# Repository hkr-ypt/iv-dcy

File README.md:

# IV-DCY USB reference board

IV-DCY is a small open-source USB device: a two-layer STM32F042 board and its
firmware. The board enumerates as a USB CDC-ACM serial port and answers a few
text commands (`PING`, `VERSION`, `INFO`, ...).

This project is the public reference implementation of the IV-DCY USB
identity: the vendor/product ID, the descriptors and the CDC-ACM command
interface. **It is not a measurement instrument.** The board has no
current–voltage (I–V) or other measurement hardware, and the firmware has no
measurement, calibration or instrument-control code. Everything here is a
complete, minimal USB device in its own right.

| | |
|---|---|
| USB ID | VID `0x1209` (pid.codes), PID `0x6767`: the PID this project will request from pid.codes. **Not yet assigned.** |
| USB function | USB 2.0 full speed, one CDC-ACM interface (virtual serial port), bus powered |
| MCU | STMicroelectronics STM32F042K6T6 (Cortex-M0, 48 MHz, 32 KiB flash, 6 KiB RAM, crystal-less USB) |
| Board | 28 × 36 mm, 2 layers, 18 components, USB-C |
| Licences | hardware CERN-OHL-S-2.0, firmware/software MIT (see [Licensing](#licensing)) |
| Status | Designed and checked in software only. **Not yet fabricated or tested on hardware**; see [docs/verification.md](docs/verification.md). |

## What the hardware does

The board is a bus-powered USB device with nothing on it but what a USB
device needs:

| Ref | Part | Purpose |
|---|---|---|
| J1 | GCT USB4105-GF-A USB-C receptacle (USB 2.0) | USB connection. The 5.1 kΩ R1/R2 on CC1/CC2 identify the board as a USB-C sink, so hosts supply 5 V. |
| U3 | ST USBLC6-2SC6 | ESD protection on D+/D− (flow-through layout), referenced to VBUS |
| U2, C1, C2 | Microchip MCP1700-3.3 LDO, 1 µF / 4.7 µF | 3.3 V from VBUS |
| U1, C3–C7 | ST STM32F042K6T6 + decoupling and NRST capacitor | USB full-speed device with on-chip D+ pull-up. Its 48 MHz RC oscillator is trimmed to the USB frame clock, so no crystal is needed. |
| SW1, R3 | BOOT push-button, 10 kΩ pull-down on PB8/BOOT0 | Held while plugging in: starts ST's USB DFU bootloader in ROM. Afterwards it is readable as a button. |
| D1, R4 | green LED on PA4 | status |
| J2 | ARM Cortex 10-pin 1.27 mm header | SWD programming/debugging |

Schematic: [hardware/docs/iv_dcy-schematic.pdf](hardware/docs/iv_dcy-schematic.pdf).
BOM: [hardware/bom/iv_dcy-bom.csv](hardware/bom/iv_dcy-bom.csv).
Design notes: [hardware/README.md](hardware/README.md).

## What the firmware does

The firmware sets up the 48 MHz clock and USB, then runs the TinyUSB device
stack. It enumerates as a CDC-ACM serial port and replies to line-based
commands:

| Command | Reply |
|---|---|
| `PING` | `PONG` |
| `VERSION` | firmware version, e.g. `0.1.0` |
| `INFO` | `IV-DCY USB reference fw=0.1.0 vid=0x1209 pid=0x6767 serial=<24 hex digits>` |
| `LED ON` / `LED OFF` / `LED AUTO` | `OK` (AUTO: LED shows the USB state) |
| `BUTTON` | `PRESSED` or `RELEASED` |
| `HELP` | list of commands |

The full descriptor and protocol description is in
[docs/usb-interface.md](docs/usb-interface.md). The firmware is about 11 KiB.
Build, test and flashing details are in [firmware/README.md](firmware/README.md).

## Repository layout

```
hardware/            board design (CERN-OHL-S-2.0)
  skidl/             circuit source (SKiDL) + schematic writer
  layout/            PCB placement and routing source (KiCad pcbnew script)
  kicad/             generated, editable KiCad 9 project: .kicad_sch, .kicad_pcb, .net
  bom/ fab/ docs/    BOM, Gerbers + drill + pick-and-place, schematic PDF, renders
  reports/           ERC and DRC reports of the committed design
  scripts/           netlist comparison and packaging helpers
  build.sh           regenerate everything and run all checks
firmware/            STM32F042 firmware (MIT)
  src/               application, board support, USB descriptors, start-up, linker script
  tests/             host unit tests (CTest)
  tools/             iv_dcy_check.py: host-side test over the serial port
docs/                USB interface, verification status, third-party components
LICENSES/            licence texts
```

## Building the hardware

You need KiCad 9 (with `kicad-cli` and its `pcbnew` Python module) and SKiDL 2.2.3.

```bash
python3 -m venv --system-site-packages .venv
```

```bash
.venv/bin/pip install -r hardware/requirements.txt
```

```bash
PYTHON=.venv/bin/python hardware/build.sh
```

`build.sh` regenerates the netlist and schematic from `hardware/skidl/iv_dcy.py`
and runs KiCad ERC. It then checks that the schematic's netlist equals the
SKiDL netlist, and rebuilds the routed PCB from `hardware/layout/place_route.py`.
Next it runs KiCad DRC, including schematic-parity checking, and stops on any
error or warning. Finally it writes the BOM, Gerbers, drill and position files.
The KiCad files in `hardware/kicad/` can also be opened and edited directly in
KiCad 9. See [hardware/README.md](hardware/README.md).

## Building and flashing the firmware

You need CMake ≥ 3.24, `arm-none-eabi-gcc` and git. The pinned dependencies
(TinyUSB, CMSIS) are fetched automatically at configure time.

```bash
cmake -S firmware -B build/firmware
```

```bash
cmake --build build/firmware
```

To flash over USB without a programmer, hold **BOOT**, plug the board in,
release the button, then run:

```bash
dfu-util -a 0 -s 0x08000000:leave -D build/firmware/iv_dcy.bin
```

To flash over SWD (ST-LINK, CMSIS-DAP, ...) via J2 with OpenOCD:

```bash
openocd -f interface/stlink.cfg -f target/stm32f0x.cfg -c "program build/firmware/iv_dcy.elf verify reset exit"
```

Host unit tests:

```bash
cmake -S firmware/tests -B build/tests && cmake --build build/tests && ctest --test-dir build/tests
```

## Talking to the device

The board appears as `/dev/ttyACM*` (Linux), `/dev/cu.usbmodem*` (macOS) or a
`COM` port (Windows 10 and later use the built-in `usbser` driver). Any
terminal works; the baud rate is ignored. Commands end with Enter and the
device does not echo. To run the scripted check:

```bash
pip install pyserial && python3 firmware/tools/iv_dcy_check.py
```

## Changing the VID/PID

The USB identity is defined in exactly one place,
[`firmware/src/usb_identity.h`](firmware/src/usb_identity.h): `USB_VID`,
`USB_PID`, the descriptor strings and the firmware version. The descriptors,
the `INFO` reply and `tools/iv_dcy_check.py` all read it. A unit test fails if
the VID or PID literal appears in any other firmware source. Until pid.codes
has assigned the PID, set `USB_PID` to the pid.codes test PID `0x0001` for any
board that leaves your own desk.

## Testing status

Everything that can be checked without hardware has been checked: ERC, DRC,
schematic/netlist parity, a clean firmware build, unit tests of the
descriptors and command parser, and an inspection of the linked image. **No
board has been built yet.** USB enumeration, the bootloader entry, the LED,
the button and the power supply have not been observed on real hardware, and
no USB-IF compliance testing has been done. The full list is in
[docs/verification.md](docs/verification.md).

## Licensing

| What | Licence |
|---|---|
| `hardware/` (circuit source, layout source, KiCad files, generated outputs, hardware scripts) | [CERN-OHL-S-2.0](LICENSES/CERN-OHL-S-2.0.txt) |
| `firmware/`, `docs/` and the top-level files | [MIT](LICENSES/MIT.txt) |

Third-party components are not relicensed; they keep their own licences.
TinyUSB is MIT and CMSIS is Apache-2.0; both are fetched at build time and not
stored here. The KiCad symbols and footprints are CC-BY-SA-4.0 with the KiCad
library exception. Details and redistribution notes are in
[docs/third-party.md](docs/third-party.md).

Copyright (c) 2026 Lucas Wu.

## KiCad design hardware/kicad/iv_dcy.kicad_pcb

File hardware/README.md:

# IV-DCY hardware

A bus-powered USB-C board built around the STM32F042K6T6. Everything in this
directory is generated from two source files:

| Source | Defines | Generated |
|---|---|---|
| [`skidl/iv_dcy.py`](skidl/iv_dcy.py) | the circuit: parts, values, footprints, MPNs, nets; plus where each symbol sits on the schematic sheet | `kicad/iv_dcy.net`, `kicad/iv_dcy.kicad_sch` |
| [`layout/place_route.py`](layout/place_route.py) | the PCB: outline, placement, every track and via, GND pours, silkscreen, design rules | `kicad/iv_dcy.kicad_pcb`, `kicad/iv_dcy.kicad_pro` |

All symbols and footprints come from the stock KiCad 9 libraries. There is no
project-specific library. The KiCad files are ordinary KiCad 9 files that
can be opened and edited directly. If you edit them by hand rather than
through the Python sources, the next `build.sh` run overwrites the edits.

## Regenerating and checking the design

Requirements: KiCad 9.0 (`kicad-cli` plus the `pcbnew` Python module that
ships with it) and SKiDL 2.2.3. On Ubuntu, the `kicad` package from the
KiCad 9.0 PPA provides both KiCad and the libraries. Create a virtual
environment that can see KiCad's `pcbnew` module:

```bash
python3 -m venv --system-site-packages .venv
```

```bash
.venv/bin/pip install -r hardware/requirements.txt
```

```bash
PYTHON=.venv/bin/python hardware/build.sh
```

`build.sh` runs these steps and stops at the first failure:

1. `skidl/iv_dcy.py`: builds the circuit, runs SKiDL's ERC, and writes the
   netlist and the schematic (drawn by `skidl/kicad_sch.py`).
2. KiCad ERC on the schematic, with every check enabled. It fails on any error
   or warning. Report: `reports/erc.rpt`.
3. The schematic's netlist, exported by `kicad-cli`, is compared with the
   SKiDL netlist pad by pad (`scripts/netlist_compare.py`).
4. `layout/place_route.py` rebuilds the PCB and fills the zones.
5. KiCad DRC with schematic parity and every check enabled. It fails on any
   violation, unconnected item or parity difference. Report: `reports/drc.rpt`.
6. Outputs: `bom/iv_dcy-bom.csv`, `fab/iv_dcy-gerbers.zip` (Gerber X2 plus
   Excellon drill), `fab/iv_dcy-pos.csv` (pick-and-place, top side),
   `docs/iv_dcy-schematic.pdf`, and board images in `docs/`.

Re-running the build gives identical netlist, schematic and board files.
The UUIDs are deterministic.

## Circuit

* **USB-C (J1)**: USB 2.0 receptacle. D+ (A6/B6) and D− (A7/B7) are joined
  next to the connector, so both plug orientations work. CC1/CC2 each have a
  5.1 kΩ pull-down (R1, R2), the USB-C "sink" termination, so a USB-C host or
  charger turns VBUS on. SBU1/SBU2 are unused. The shell is tied to GND.
* **ESD (U3)**: USBLC6-2SC6 in flow-through layout (pins 1/6 = D+,
  3/4 = D−), placed between the connector and the MCU, with its VBUS pin on
  VBUS.
* **Power (U2)**: MCP1700-3.3 low-dropout regulator, VBUS to 3.3 V. C1 is
  1 µF at the input; C2 is 4.7 µF at the output. The total capacitance on
  VBUS (C1) stays far below USB's 10 µF inrush limit. The board's current
  draw has not been measured. It is expected to be a few tens of mA, well
  within both the MCP1700's 250 mA rating and the 100 mA declared in the
  USB descriptor.
* **MCU (U1)**: STM32F042K6T6 in LQFP-32. The USB D+ pull-up and the 48 MHz
  oscillator are on chip, and the clock recovery system trims that oscillator
  to the host's USB frames, so the board needs no crystal. Decoupling: C3
  (100 nF, VDD), C4 (100 nF, VDDIO2), C5 + C6 (1 µF + 10 nF, VDDA), all from
  the single 3.3 V rail. C7 (100 nF) filters NRST.
* **BOOT (SW1, R3)**: PB8 is also the BOOT0 pin on this part. R3 holds it
  low. Pressing SW1 pulls it to 3.3 V, so a board powered up with SW1 held
  starts ST's ROM USB DFU bootloader. This relies on the factory option
  bytes, which take BOOT0 from the pin. After reset, PB8 is an ordinary
  input, so the firmware can read the button.
* **LED (D1, R4)**: on PA4, active high, about 1 mA through 1 kΩ.
* **SWD (J2)**: ARM Cortex 10-pin 1.27 mm header. Pin 1 VTref (3.3 V),
  2 SWDIO, 4 SWCLK, 10 nRESET; 3/5/9 GND; 6 and 8 are not connected (the
  Cortex-M0 has no SWO).

## PCB

* 28 × 36 mm, 2 layers, 1.6 mm FR-4, 1 oz copper; all parts on the top side.
* Design rules: 0.2 mm tracks and clearance (0.4 mm for the VBUS and +3V3
  trunks), 0.6 mm
  vias with 0.3 mm drill, 0.3 mm copper-to-edge. These are within the
  standard capabilities of common low-cost PCB services.
* Both layers carry a GND pour, stitched with vias. The bottom layer is
  almost unbroken GND: only a short VBUS link behind the connector and the
  NRST connection to J2 run there.
* D+/D− run as a short, tightly coupled pair on the top layer over the bottom
  GND plane: connector, then ESD array, then MCU. Full-speed USB (12 Mbit/s)
  does not need impedance-controlled stack-up.
* The USB-C receptacle sits on the bottom board edge, as its footprint expects.
* The bottom silkscreen carries the licence and the source location, as
  CERN-OHL-S-2.0 asks of products.

## Not yet verified

This design has been checked by ERC, DRC and netlist parity only. **No board
has been fabricated, assembled or powered.** See
[../docs/verification.md](../docs/verification.md).

## Licence

CERN-OHL-S-2.0 ([text](../LICENSES/CERN-OHL-S-2.0.txt)). This source
describes Open Hardware and is licensed under the CERN-OHL-S v2. You may
redistribute and modify this source and make products using it under the
terms of the CERN-OHL-S v2. It is distributed WITHOUT ANY EXPRESS OR IMPLIED
WARRANTY, INCLUDING OF MERCHANTABILITY, SATISFACTORY QUALITY AND FITNESS FOR
A PARTICULAR PURPOSE. Source location: https://github.com/hkr-ypt/iv-dcy

The KiCad library symbols and footprints embedded in the KiCad files are
© the KiCad library contributors, CC-BY-SA-4.0 with the KiCad libraries
exception, which waives the share-alike terms for designs that use them.

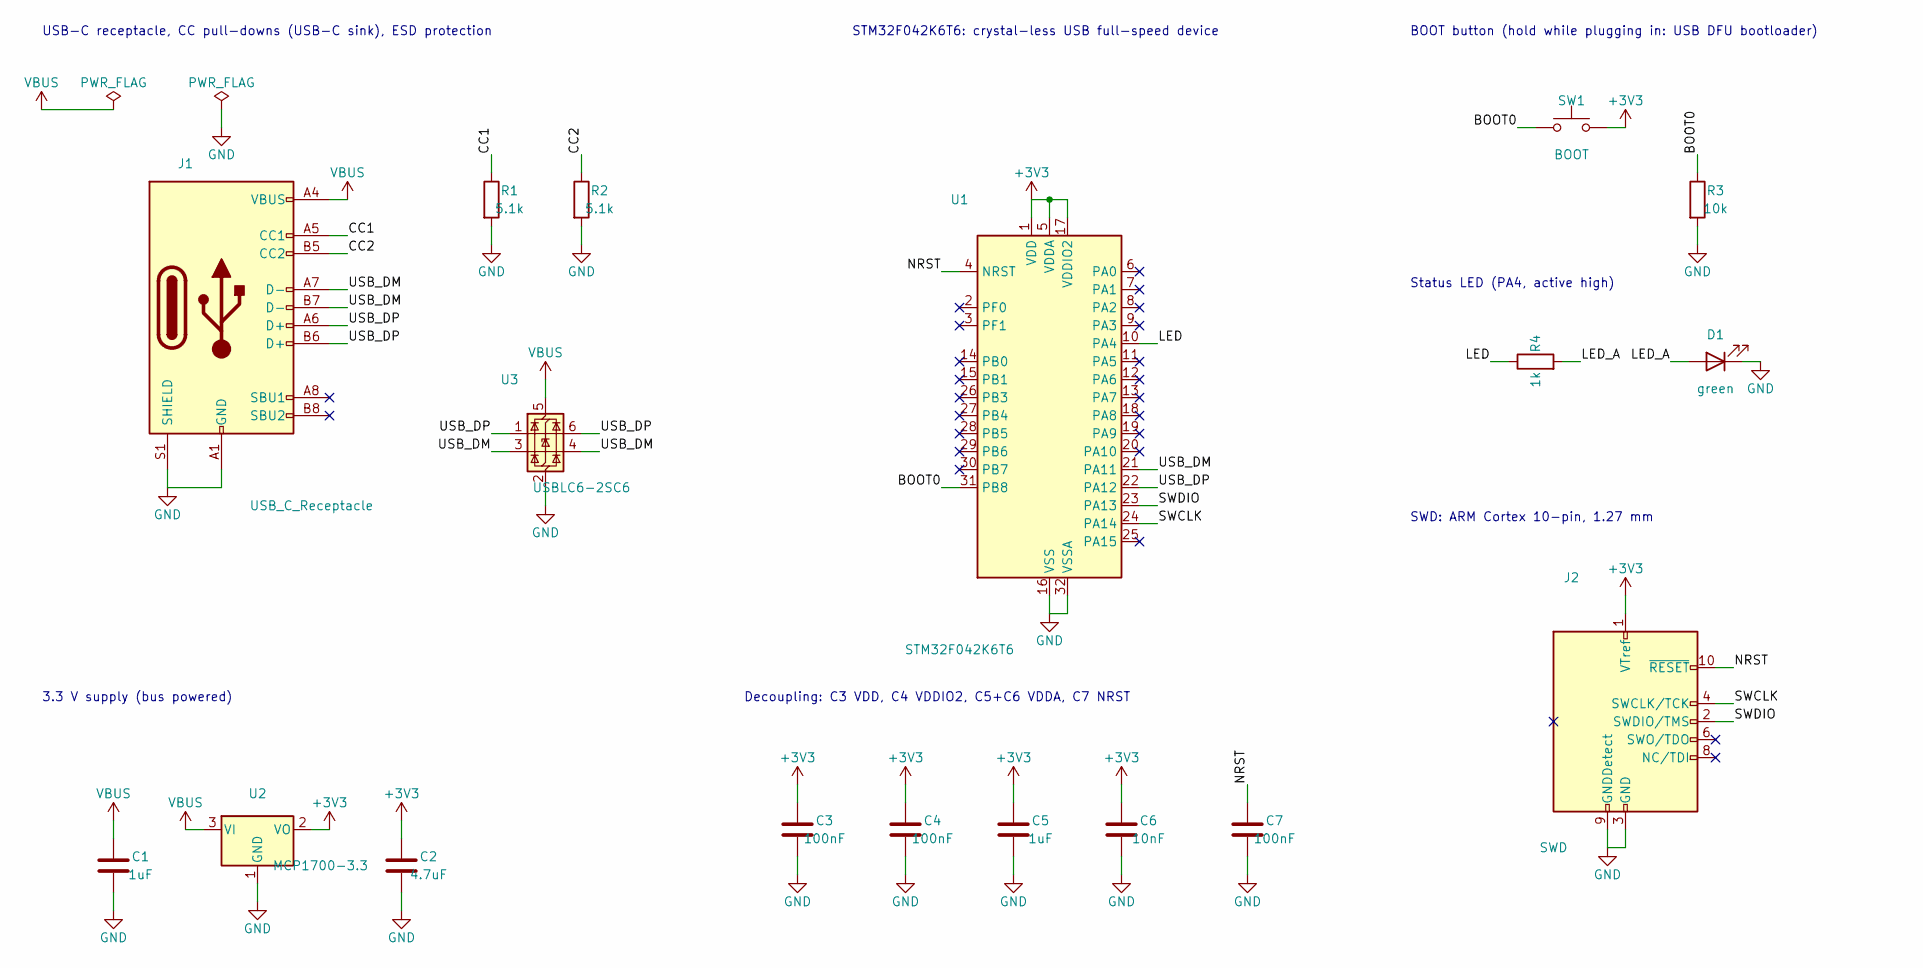
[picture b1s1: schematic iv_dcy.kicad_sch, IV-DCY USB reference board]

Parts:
C1, C5: 1uF; C_0603_1608Metric; MPN 0603 1uF 16V X5R
C2: 4.7uF; C_0603_1608Metric; MPN 0603 4.7uF 10V X5R
C3, C4, C7: 100nF; C_0603_1608Metric; MPN 0603 100nF 16V X7R
C6: 10nF; C_0603_1608Metric; MPN 0603 10nF 50V X7R
D1: green; LED_0603_1608Metric; MPN 0603 green LED
J1: USB_C_Receptacle; USB_C_Receptacle_GCT_USB4105-xx-A_16P_TopMnt_Horizontal; MPN GCT USB4105-GF-A
J2: SWD; PinHeader_2x05_P1.27mm_Vertical; MPN Samtec FTSH-105-01-L-DV (or equivalent)
R1, R2: 5.1k; R_0603_1608Metric; MPN 0603 5.1k 1%
R3: 10k; R_0603_1608Metric; MPN 0603 10k 1%
R4: 1k; R_0603_1608Metric; MPN 0603 1k 1%
SW1: BOOT; SW_SPST_B3U-1000P; MPN Omron B3U-1000P
U1: STM32F042K6T6; LQFP-32_7x7mm_P0.8mm; MPN STMicroelectronics STM32F042K6T6
U2: MCP1700-3.3; SOT-23; MPN Microchip MCP1700T-3302E/TT
U3: USBLC6-2SC6; SOT-23-6; MPN STMicroelectronics USBLC6-2SC6

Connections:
+3V3: C2.1, C3.1, C4.1, C5.1, C6.1, J2.1 (VTref), SW1.2, U1.1 (VDD), U1.5 (VDDA), U1.17 (VDDIO2), U2.2 (VO)
/BOOT0: R3.1, SW1.1, U1.31 (PB8)
/CC1: J1.A5 (CC1), R1.1
/CC2: J1.B5 (CC2), R2.1
/LED: R4.1, U1.10 (PA4)
/LED_A: D1.2 (A), R4.2
/NRST: C7.1, J2.10 (~RESET), U1.4 (NRST)
/SWCLK: J2.4 (SWCLK/TCK), U1.24 (PA14)
/SWDIO: J2.2 (SWDIO/TMS), U1.23 (PA13)
/USB_DM: J1.A7 (D-), J1.B7 (D-), U1.21 (PA11), U3.3 (I/O2), U3.4 (I/O2)
/USB_DP: J1.A6 (D+), J1.B6 (D+), U1.22 (PA12), U3.1 (I/O1), U3.6 (I/O1)
GND: C1.2, C2.2, C3.2, C4.2, C5.2, C6.2, C7.2, D1.1 (K), J1.A1 (GND), J1.A12 (GND), J1.B1 (GND), J1.B12 (GND), J1.S1 (SHIELD), J2.3 (GND), J2.5 (GND), J2.9 (GNDDetect), R1.2, R2.2, R3.2, U1.16 (VSS), U1.32 (VSSA), U2.1 (GND), U3.2 (GND)
VBUS: C1.1, J1.A4 (VBUS), J1.A9 (VBUS), J1.B4 (VBUS), J1.B9 (VBUS), U2.3 (VI), U3.5 (VBUS)

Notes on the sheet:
USB-C receptacle, CC pull-downs (USB-C sink), ESD protection
3.3 V supply (bus powered)
STM32F042K6T6: crystal-less USB full-speed device
Decoupling: C3 VDD, C4 VDDIO2, C5+C6 VDDA, C7 NRST
BOOT button (hold while plugging in: USB DFU bootloader)
Status LED (PA4, active high)
SWD: ARM Cortex 10-pin, 1.27 mm

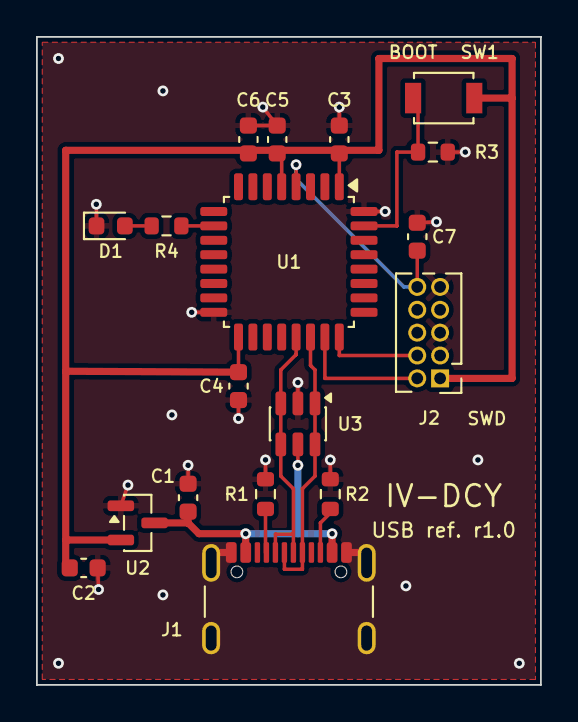
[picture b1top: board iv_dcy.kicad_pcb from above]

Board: 2 copper layers, 28.0 x 36.0 mm, 18 parts (0 on the bottom side), 13 nets.

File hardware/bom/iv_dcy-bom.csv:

"Reference","Value","Footprint","MPN","Qty"
"C1,C5","1uF","Capacitor_SMD:C_0603_1608Metric","0603 1uF 16V X5R","2"
"C2","4.7uF","Capacitor_SMD:C_0603_1608Metric","0603 4.7uF 10V X5R","1"
"C3,C4,C7","100nF","Capacitor_SMD:C_0603_1608Metric","0603 100nF 16V X7R","3"
"C6","10nF","Capacitor_SMD:C_0603_1608Metric","0603 10nF 50V X7R","1"
"D1","green","LED_SMD:LED_0603_1608Metric","0603 green LED","1"
"J1","USB_C_Receptacle","Connector_USB:USB_C_Receptacle_GCT_USB4105-xx-A_16P_TopMnt_Horizontal","GCT USB4105-GF-A","1"
"J2","SWD","Connector_PinHeader_1.27mm:PinHeader_2x05_P1.27mm_Vertical","Samtec FTSH-105-01-L-DV (or equivalent)","1"
"R1,R2","5.1k","Resistor_SMD:R_0603_1608Metric","0603 5.1k 1%","2"
"R3","10k","Resistor_SMD:R_0603_1608Metric","0603 10k 1%","1"
"R4","1k","Resistor_SMD:R_0603_1608Metric","0603 1k 1%","1"
"SW1","BOOT","Button_Switch_SMD:SW_SPST_B3U-1000P","Omron B3U-1000P","1"
"U1","STM32F042K6T6","Package_QFP:LQFP-32_7x7mm_P0.8mm","STMicroelectronics STM32F042K6T6","1"
"U2","MCP1700-3.3","Package_TO_SOT_SMD:SOT-23","Microchip MCP1700T-3302E/TT","1"
"U3","USBLC6-2SC6","Package_TO_SOT_SMD:SOT-23-6","STMicroelectronics USBLC6-2SC6","1"

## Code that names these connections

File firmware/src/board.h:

/* SPDX-License-Identifier: MIT
 * Copyright (c) 2026 Lucas Wu
 *
 * Board support for the IV-DCY USB reference board (STM32F042K6T6).
 *
 *   PA4         status LED, active high (D1 via R4)
 *   PB8/BOOT0   BOOT button, high while pressed (R3 pull-down)
 *   PA11/PA12   USB D-/D+ (USB full-speed device, internal D+ pull-up)
 *   PA13/PA14   SWDIO/SWCLK
 */
#ifndef BOARD_H
#define BOARD_H

#include <stdbool.h>
#include <stdint.h>

void board_init(void);          /* clocks (HSI48 + CRS), SysTick, GPIO, USB clock */
uint32_t board_millis(void);    /* milliseconds since board_init() */
void board_led(bool on);
bool board_button(void);
void board_uid(uint32_t uid[3]);   /* 96-bit factory unique ID */

#endif /* BOARD_H */
